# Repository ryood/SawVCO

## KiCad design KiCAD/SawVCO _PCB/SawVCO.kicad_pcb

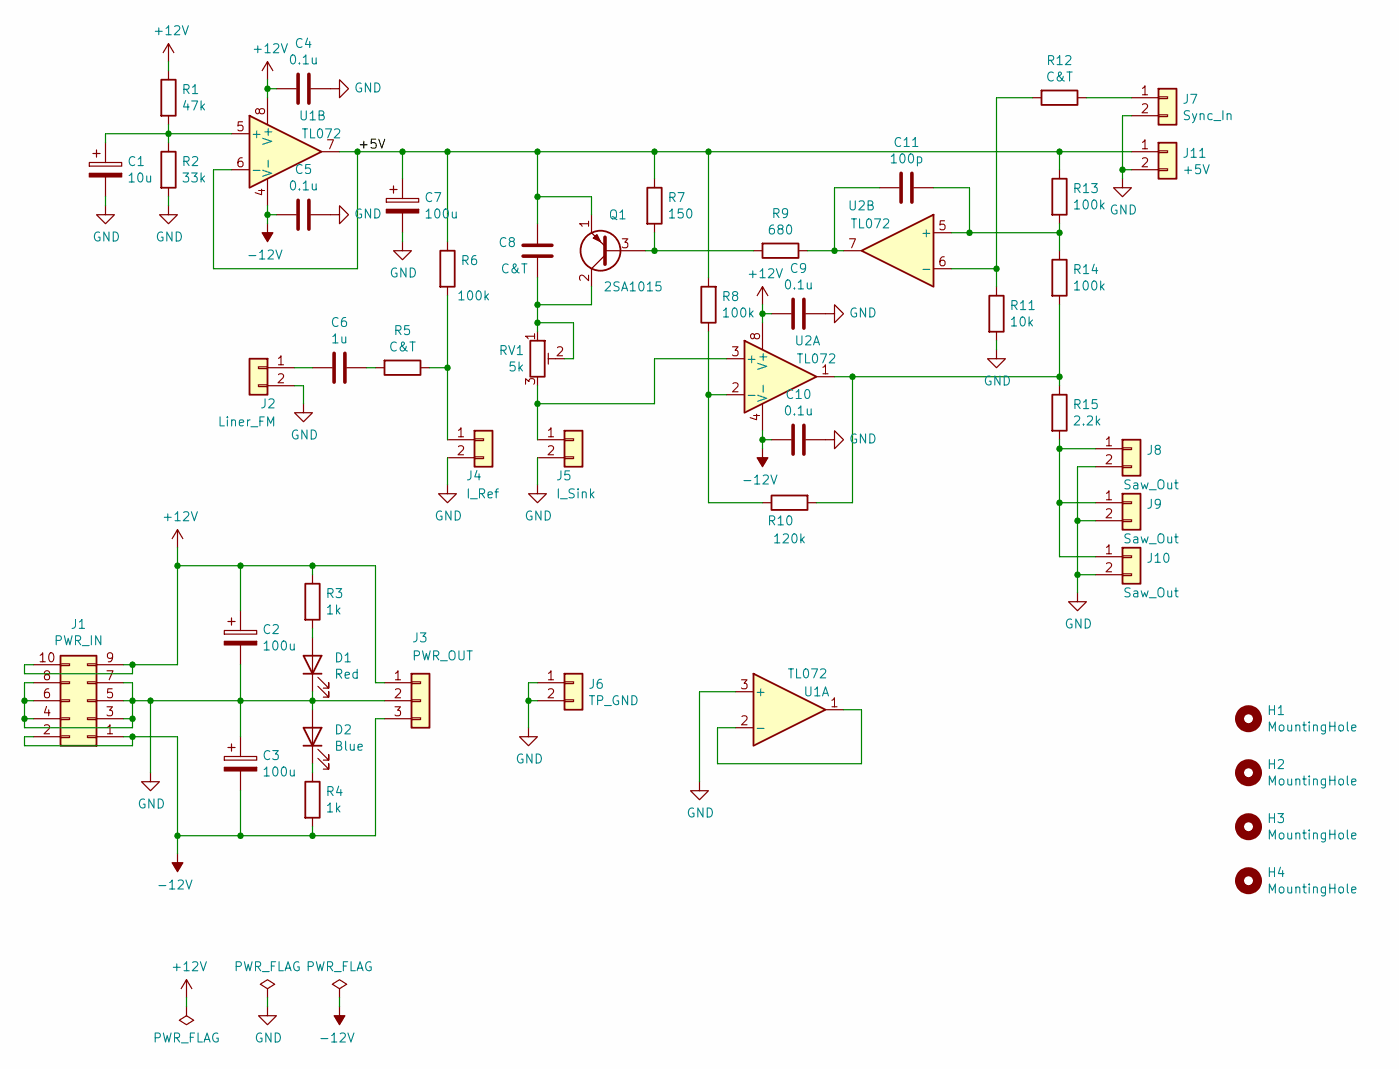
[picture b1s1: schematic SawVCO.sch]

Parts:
C1: 10u; CP_Radial_D5.0mm_P2.50mm
C2, C3, C7: 100u; CP_Radial_D6.3mm_P2.50mm
C4, C5, C9, C10: 0.1u; C_Disc_D3.0mm_W1.6mm_P2.50mm
C6: 1u; C_Rect_L7.2mm_W4.5mm_P5.00mm_FKS2_FKP2_MKS2_MKP2
C8: C&T; C_Rect_L7.2mm_W3.5mm_P5.00mm_FKS2_FKP2_MKS2_MKP2
C11: 100p; C_Disc_D4.3mm_W1.9mm_P5.00mm
D1: Red; LED_D3.0mm
D2: Blue; LED_D3.0mm
H1, H2, H3, H4: MountingHole; MountingHole_3.2mm_M3
J1: PWR_IN; IDC-Header_2x05_P2.54mm_Vertical
J2: Liner_FM; JST_XH_B2B-XH-A_1x02_P2.50mm_Vertical
J3: PWR_OUT; JST_XH_B3B-XH-A_1x03_P2.50mm_Vertical
J4: I_Ref; JST_XH_B2B-XH-A_1x02_P2.50mm_Vertical
J5: I_Sink; JST_XH_B2B-XH-A_1x02_P2.50mm_Vertical
J6: TP_GND; PinHeader_1x02_P2.54mm_Vertical
J7: Sync_In; JST_XH_B2B-XH-A_1x02_P2.50mm_Vertical
J8, J9, J10: Saw_Out; JST_XH_B2B-XH-A_1x02_P2.50mm_Vertical
J11: +5V; JST_XH_B2B-XH-A_1x02_P2.50mm_Vertical
Q1: 2SA1015; TO-92_Wide
R1: 47k; R_Axial_DIN0207_L6.3mm_D2.5mm_P7.62mm_Horizontal
R2: 33k; R_Axial_DIN0207_L6.3mm_D2.5mm_P7.62mm_Horizontal
R3, R4: 1k; R_Axial_DIN0207_L6.3mm_D2.5mm_P7.62mm_Horizontal
R5, R12: C&T; R_Axial_DIN0207_L6.3mm_D2.5mm_P7.62mm_Horizontal
R6, R8, R13, R14: 100k; R_Axial_DIN0207_L6.3mm_D2.5mm_P7.62mm_Horizontal
R7: 150; R_Axial_DIN0207_L6.3mm_D2.5mm_P7.62mm_Horizontal
R9: 680; R_Axial_DIN0207_L6.3mm_D2.5mm_P7.62mm_Horizontal
R10: 120k; R_Axial_DIN0207_L6.3mm_D2.5mm_P7.62mm_Horizontal
R11: 10k; R_Axial_DIN0207_L6.3mm_D2.5mm_P7.62mm_Horizontal
R15: 2.2k; R_Axial_DIN0207_L6.3mm_D2.5mm_P7.62mm_Horizontal
RV1: 5k; Potentiometer_Bourns_3296X_Horizontal
U1, U2: TL072; DIP-8_W7.62mm_Socket

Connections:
+12V: C2.1, C4.2, C9.2, J1.9, J1.10, J3.1, R1.1, R3.1, U1.8 (V+), U2.8 (V+)
-12V: C3.2, C5.2, C10.2, J1.1, J1.2, J3.3, R4.2, U1.4 (V-), U2.4 (V-)
/+5V: C7.1, C8.2, J11.1, Q1.1 (E), R6.1, R7.1, R8.2, R13.1, U1.6 (-), U1.7
GND: C1.2, C2.2, C3.1, C4.1, C5.1, C7.2, C9.1, C10.1, D1.1 (K), D2.2 (A), J1.3, J1.4, J1.5, J1.6, J1.7, J1.8, J2.2, J3.2, J4.2, J5.2, J6.1, J6.2, J7.2, J8.2, J9.2, J10.2, J11.2, R2.2, R11.2, U1.3 (+)
unnamed: C1.1, R1.2, R2.1, U1.5 (+)
unnamed: C6.1, R5.2
unnamed: C6.2, J2.1
unnamed: C8.1, Q1.2 (C), RV1.1, RV1.2
unnamed: C11.1, R13.2, R14.1, U2.5 (+)
unnamed: C11.2, R9.1, U2.7
unnamed: D1.2 (A), R3.2
unnamed: D2.1 (K), R4.1
unnamed: J4.1, R5.1, R6.2
unnamed: J5.1, RV1.3, U2.3 (+)
unnamed: J7.1, R12.1
unnamed: J8.1, J9.1, J10.1, R15.2
unnamed: Q1.3 (B), R7.2, R9.2
unnamed: R8.1, R10.1, U2.2 (-)
unnamed: R10.2, R14.2, R15.1, U2.1
unnamed: R11.1, R12.2, U2.6 (-)
unnamed: U1.1, U1.2 (-)

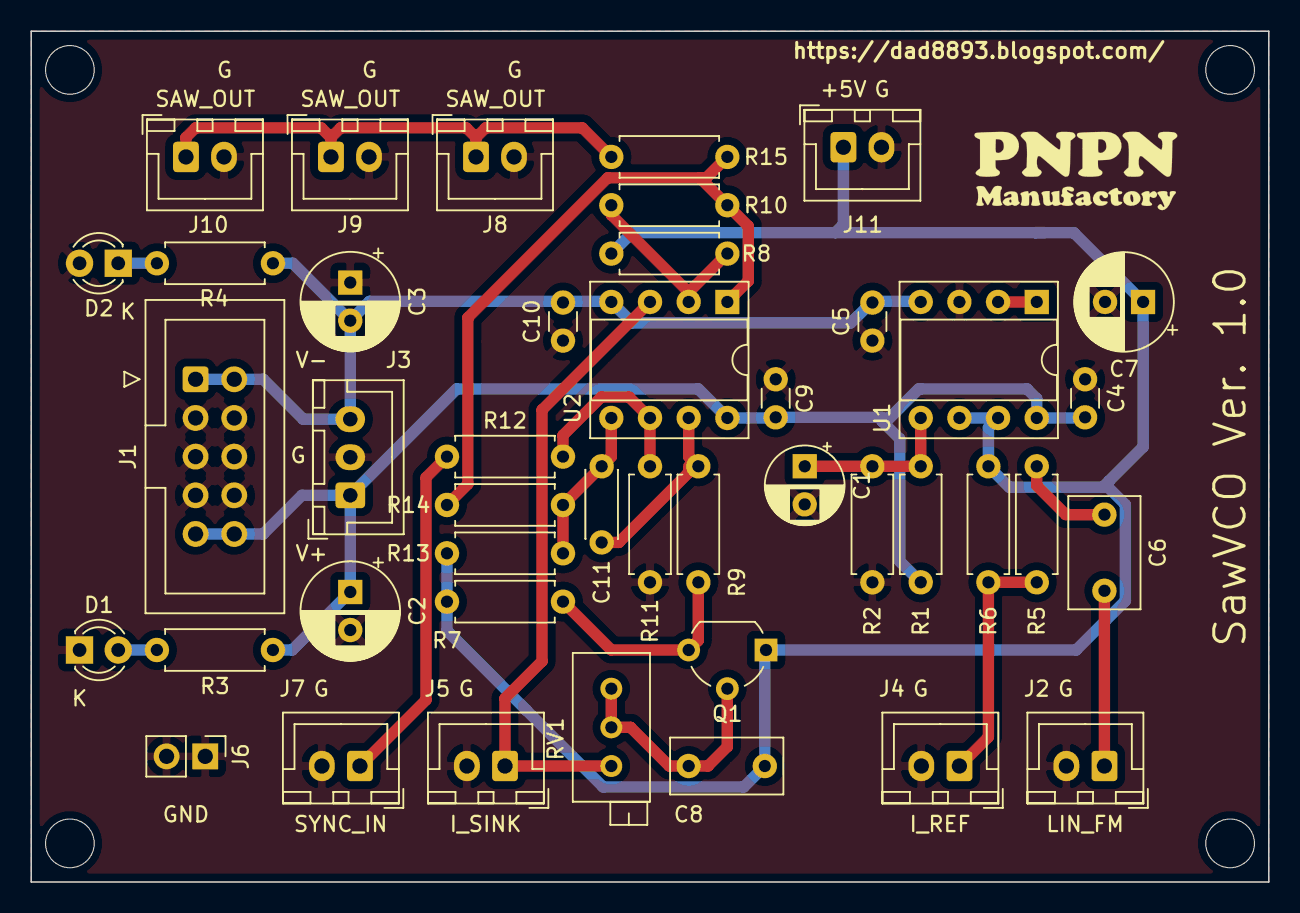
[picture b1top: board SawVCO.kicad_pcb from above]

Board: 2 copper layers, 81.3 x 55.9 mm, 47 parts (0 on the bottom side), 21 nets.

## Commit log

2020-10-19 SawVCO_PCB
2020-10-19 Add +5V Output
2020-12-12 結合テスト
2020-12-23 Rack mount
2021-02-10 Panel design
2021-02-10 Update: Panel Design
2021-02-13 Update: Panel design of Antilog-NPNO Ver.1.2
2021-02-28 Add: SawVCO_Antilog_Ver_1_2_Panel design
